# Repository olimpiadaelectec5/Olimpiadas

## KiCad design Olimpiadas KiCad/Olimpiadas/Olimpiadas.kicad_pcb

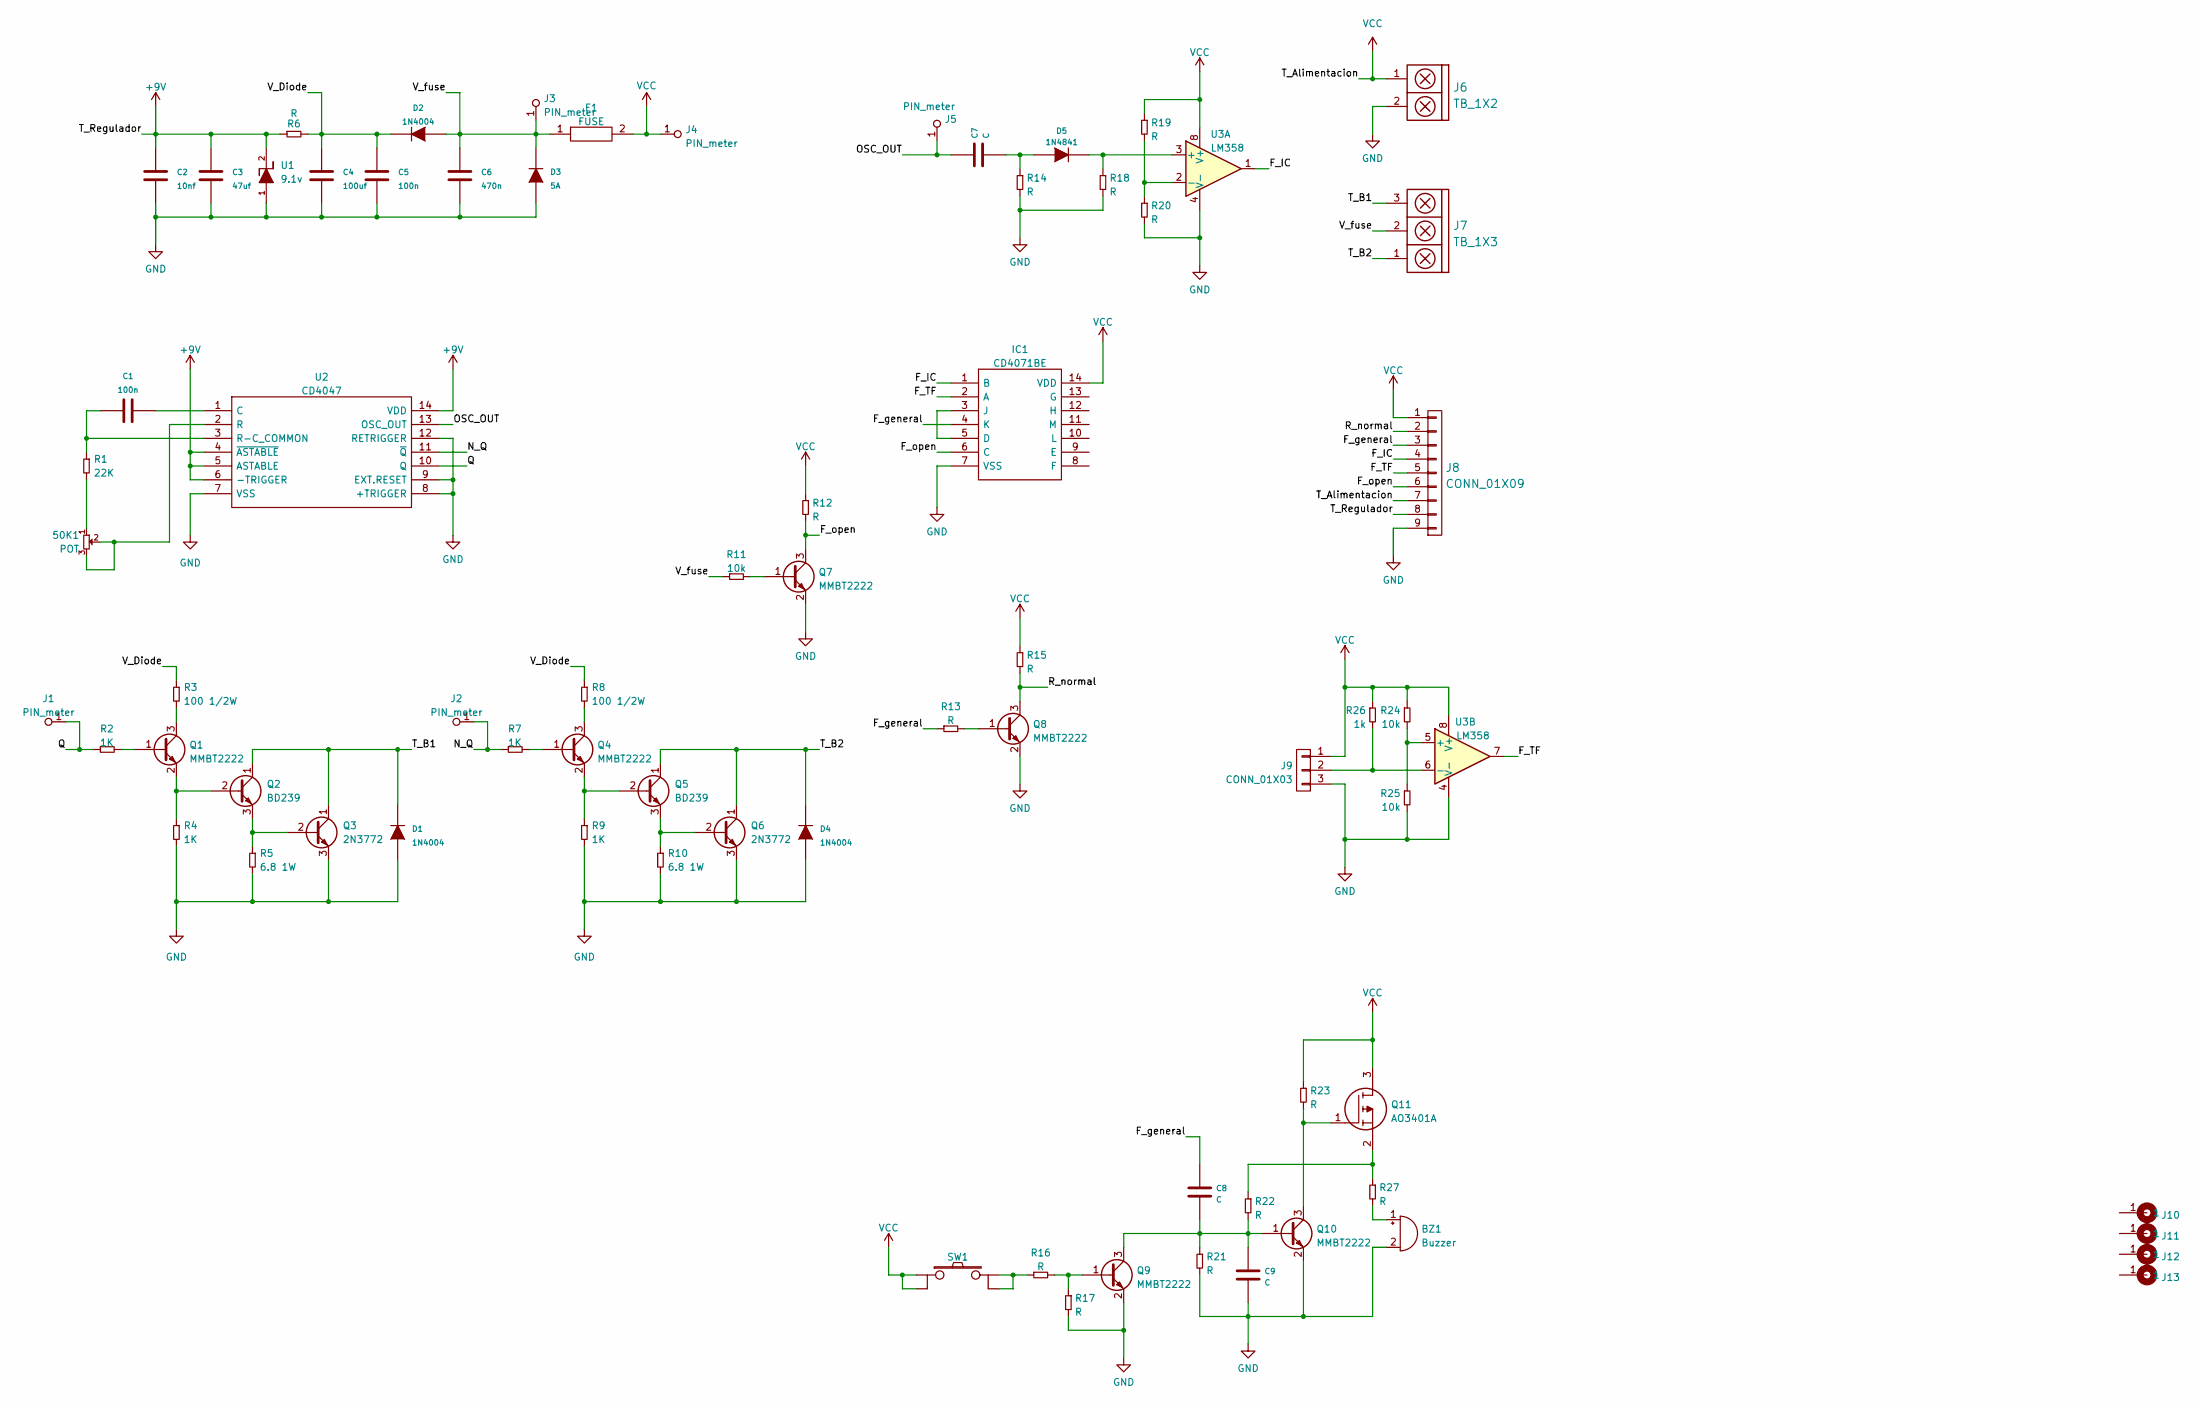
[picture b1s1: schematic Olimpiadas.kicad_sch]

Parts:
50K1: POT; TRIMER_V
BZ1: Buzzer; Buzzer_12mm
C1, C5: 100n; CAP_0.1
C2: 10nf; CAP_0.1
C3: 47uf; CAP_ELEC_5x11mm
C4: 100uf; CAP_ELEC_5x11mm
C6: 470n; CAP_0.1
C7, C8, C9: C; CAP_ELEC_5x11mm
D1, D2, D4: 1N4004; DO-41
D3: 5A; DO-41
D5: 1N4841; SOD80C
F1: FUSE; FUSIBLE
IC1: CD4071BE; DIP-14; Manufacturer_Part_Number CD4071BE; Mouser Part Number 595-CD4071BE
J1, J2, J3, J4, J5: PIN_meter; PIN_M
J6: TB_1X2; BORNERA2_AZUL
J7: TB_1X3; BORNERA3_AZUL
J8: CONN_01X09; PIN_STRIP_9
J9: CONN_01X03; Pin_Header_3
J10, J11, J12, J13: Cable_PAD; Tornillo_M3_8mm
Q1, Q4, Q7, Q8, Q9, Q10: MMBT2222; SOT23
Q2, Q5: BD239; TO-220
Q3, Q6: 2N3772; TREE_HOLES
Q11: AO3401A; SOT23; Manufacturer_Part_Number AO3401A
R1: 22K; R_0805
R2, R4, R7, R9: 1K; R_0805
R3, R8: 100 1/2W; RES0.3
R5, R10: 6.8 1W; RES0.3
R6, R12, R13, R14, R15, R16, R17, R18, R19, R20, R21, R22, R23, R27: R; R_0805
R11, R24, R25: 10k; R_0805
R26: 1k; R_0805
SW1: SW_PUSH; Pulsador_TH_4
U1: 9.1v; DO-41
U2: CD4047; DIP-14; Manufacturer_Part_Number CD4047BEE4; Mouser Part Number 595-CD4047BEE4
U3: LM358; DIP-8

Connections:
+9V: C2.1, C3.1, J8.8, R6.1, U1.2 (K), U2.4 (~ASTABLE), U2.5 (ASTABLE), U2.6 (-TRIGGER), U2.14 (VDD)
/F_IC: IC1.1 (B), J8.4, U3.1
/F_TF: IC1.2 (A), J8.5, U3.7
/F_general: C8.2, IC1.4 (K), J8.3, R13.1
/F_open: IC1.6 (C), J8.6, Q7.3 (C), R12.2
/N_Q: J2.1, R7.1, U2.11 (~Q)
/OSC_OUT: C7.1, J5.1, U2.13 (OSC_OUT)
/Q: J1.1, R2.1, U2.10 (Q)
/R_normal: J8.2, Q8.3 (C), R15.2
/T_B1: D1.2 (K), J7.3, Q2.1 (C), Q3.1 (C)
/T_B2: D4.2 (K), J7.1, Q5.1 (C), Q6.1 (C)
/V_Diode: C4.1, C5.1, D2.2 (K), R3.1, R6.2, R8.1
/V_fuse: C6.1, D2.1 (A), D3.2 (K), F1.1, J3.1, J7.2, R11.1
GND: BZ1.2 (+), C2.2, C3.2, C4.2, C5.2, C6.2, C9.2, D1.1 (A), D3.1 (A), D4.1 (A), IC1.7 (VSS), J6.2, J8.9, J9.3, Q3.3 (E), Q6.3 (E), Q7.2 (E), Q8.2 (E), Q9.2 (E), Q10.2 (E), R4.2, R5.2, R9.2, R10.2, R14.2, R17.2, R18.2, R20.2, R21.2, R25.2, U1.1 (A), U2.7 (VSS), U2.8 (+TRIGGER), U2.9 (EXT.RESET), U2.12 (RETRIGGER), U3.4 (V-)
unnamed: 50K1.1, R1.2
unnamed: 50K1.2, 50K1.3, U2.2 (R)
unnamed: BZ1.1 (-), R27.2
unnamed: C1.1, R1.1, U2.3 (R-C_COMMON)
unnamed: C1.2, U2.1 (C)
unnamed: C7.2, D5.1 (A), R14.1
unnamed: C8.1, C9.1, Q9.3 (C), Q10.1 (B), R21.1, R22.2
unnamed: D5.2 (K), R18.1, U3.3 (+)
unnamed: IC1.3 (J), IC1.5 (D)
unnamed: J9.2, R26.2, U3.6 (-)
unnamed: Q1.1 (B), R2.2
unnamed: Q1.2 (E), Q2.2 (B), R4.1
unnamed: Q1.3 (C), R3.2
unnamed: Q2.3 (E), Q3.2 (B), R5.1
unnamed: Q4.1 (B), R7.2
unnamed: Q4.2 (E), Q5.2 (B), R9.1
unnamed: Q4.3 (C), R8.2
unnamed: Q5.3 (E), Q6.2 (B), R10.1
unnamed: Q7.1 (B), R11.2
unnamed: Q8.1 (B), R13.2
unnamed: Q9.1 (B), R16.2, R17.1
unnamed: Q10.3 (C), Q11.1, R23.2
unnamed: Q11.2, R22.1, R27.1
unnamed: R16.1, SW1.3, SW1.4
unnamed: R19.2, R20.1, U3.2 (-)
unnamed: R24.2, R25.1, U3.5 (+)
VCC: F1.2, IC1.14 (VDD), J4.1, J6.1, J8.1, J8.7, J9.1, Q11.3, R12.1, R15.1, R19.1, R23.1, R24.1, R26.1, SW1.1, SW1.2, U3.8 (V+)

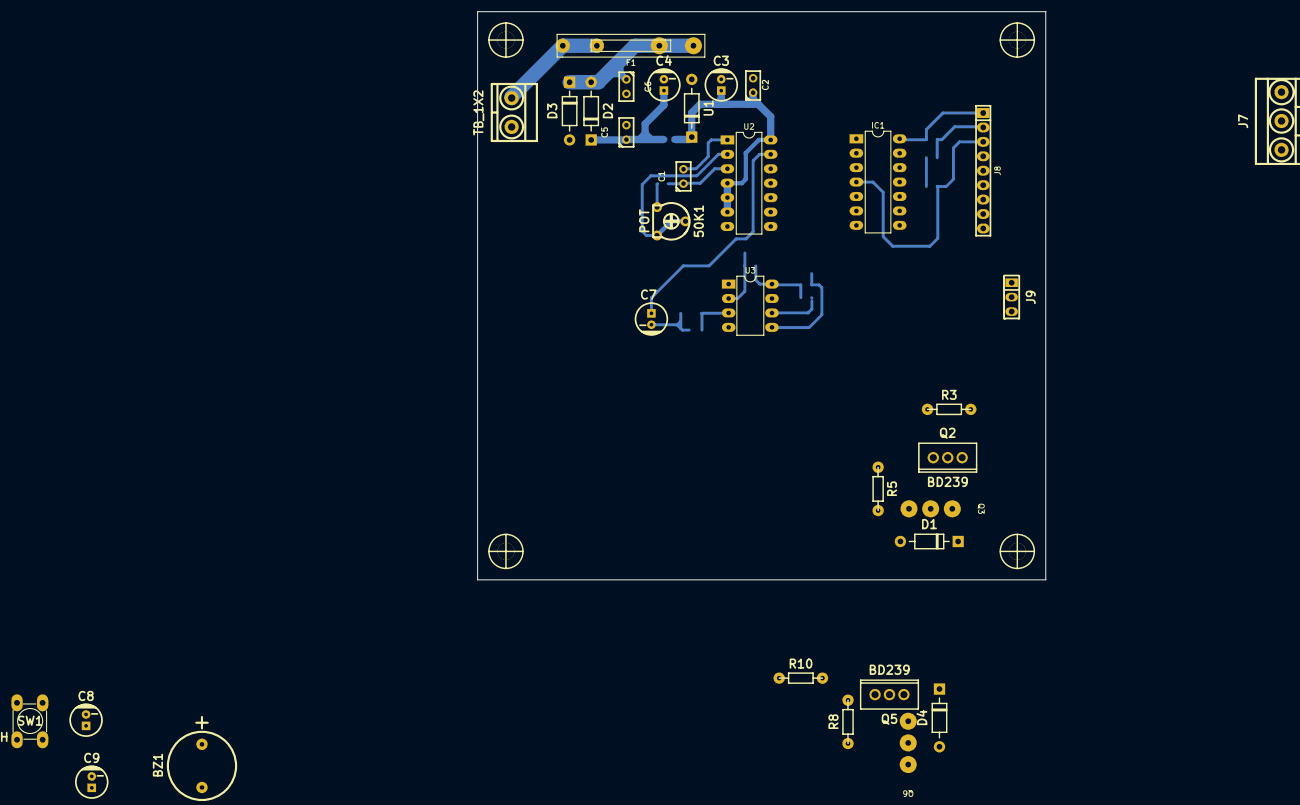
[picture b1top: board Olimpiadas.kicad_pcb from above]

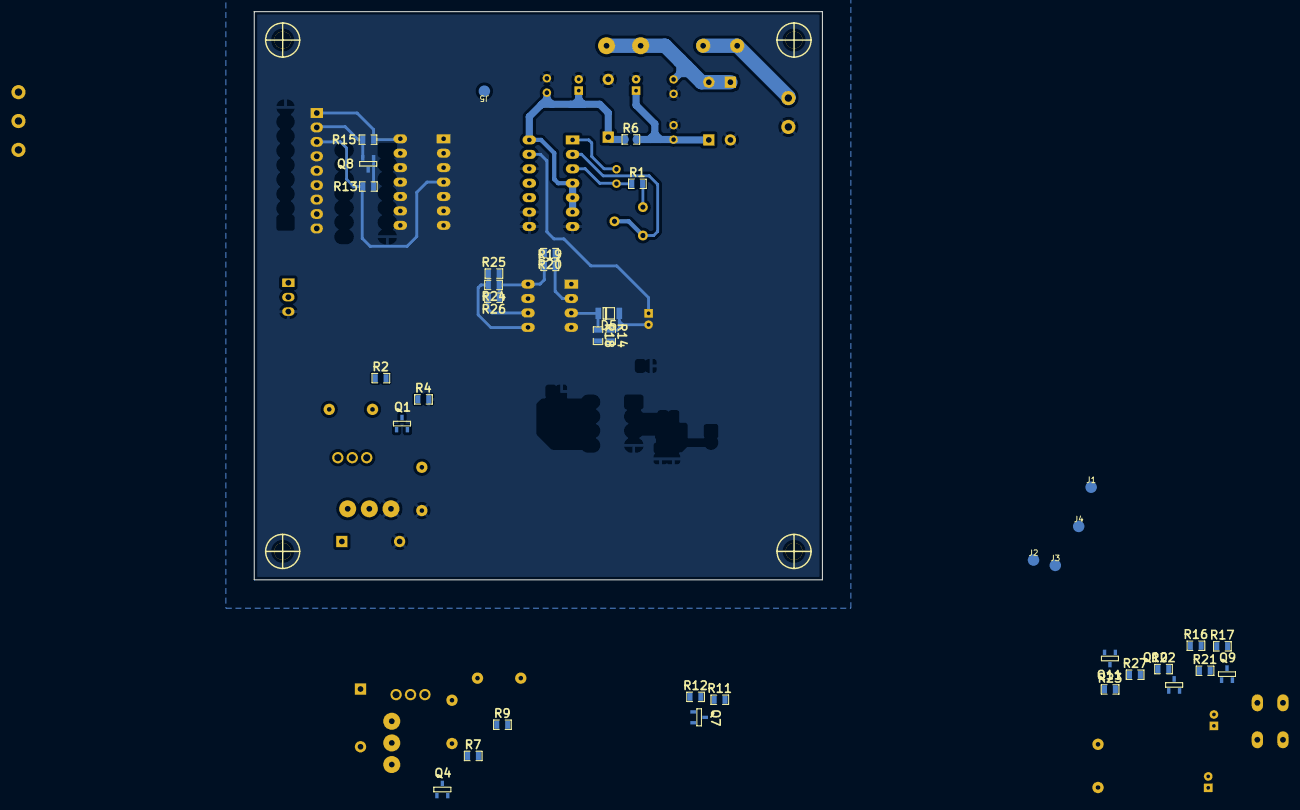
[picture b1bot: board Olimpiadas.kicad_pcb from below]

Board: 2 copper layers, 100.0 x 100.0 mm, 73 parts (36 on the bottom side), 41 nets.

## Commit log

2022-11-17 Olimpiadas
2022-11-18 PCB1
